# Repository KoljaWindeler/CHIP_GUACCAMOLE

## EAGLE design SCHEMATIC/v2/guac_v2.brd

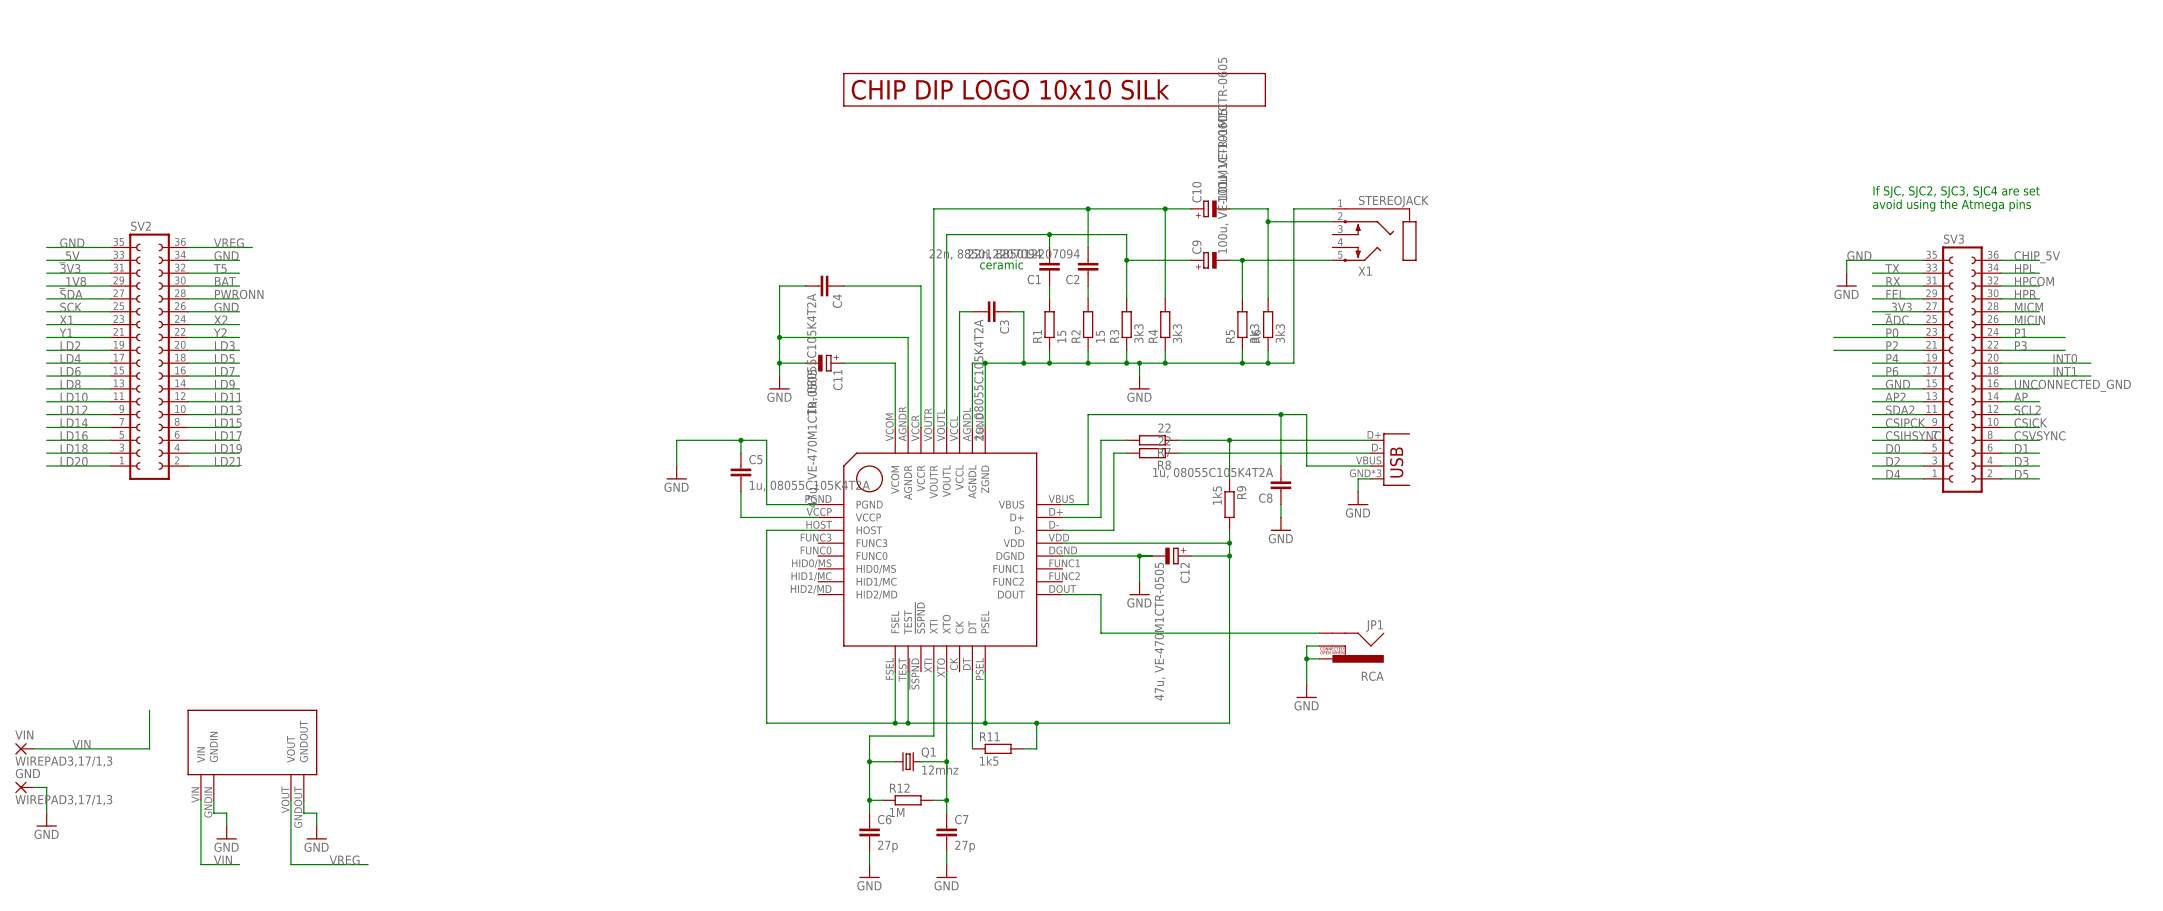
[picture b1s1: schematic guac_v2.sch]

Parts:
C1, C2: 22n, 885012207094; C0805
C3, C4, C5, C8: 1u, 08055C105K4T2A; C0805
C6, C7: 27p; C0805
C9, C10: 100u, VE-101M1CTR-0605; 140CLH-0810
C11, C12: 47u, VE-470M1CTR-0505; 140CLH-0810
GND: WIREPAD3,17/1,3; 3,17/1,3
JP1: RCA
Q1: 12mhz; HC49UP
R1, R2: 15; M0805
R3, R4, R5, R6: 3k3; M0805
R7, R8: 22; M0805
R9, R11: 1k5; M0805
R12: 1M; M0805
SV2, SV3: FE18-2
U$1: PCM2706; TQFP32-08
U$3: LOGO_10X10_SILK
U$9: MP1584EN_FRAMELESS
USB: USBUSB-MICROB-SMT-DIP; USB-MICROB-SMT-DIP
VIN: WIREPAD3,17/1,3; 3,17/1,3
X1: STEREOJACK; STX3100

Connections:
3V3: SV2.31
ADC: SV3.25
AP: SV3.14
AP2: SV3.13
BAT: SV2.30
CHIP_5V: SV3.36
CSICK: SV3.10
CSIHSYNC: SV3.7
CSIPCK: SV3.9
CSVSYNC: SV3.8
D0: SV3.5
D1: SV3.6
D2: SV3.3
D3: SV3.4
D4: SV3.1
D5: SV3.2
FEL: SV3.29
GND: C3.1, C4.2, C5.1, C6.2, C7.2, C8.1, C11.-, C12.-, GND.1, JP1.PIN, JP1.SWITCH, R1.1, R2.1, R3.1, R4.1, R5.1, R6.1, SV2.26, SV2.34, SV2.35, SV3.15, SV3.35, U$1.AGNDL, U$1.AGNDR, U$1.DGND, U$1.PGND, U$1.ZGND, U$9.GNDIN, U$9.GNDOUT, USB.GND, USB.MT1 (GND), USB.MT2 (GND), X1.1
HPCOM: SV3.32
HPL: SV3.34
HPR: SV3.30
INT0: SV3.20
INT1: SV3.18
LD2: SV2.19
LD3: SV2.20
LD4: SV2.17
LD5: SV2.18
LD6: SV2.15
LD7: SV2.16
LD8: SV2.13
LD9: SV2.14
LD10: SV2.11
LD11: SV2.12
LD12: SV2.9
LD13: SV2.10
LD14: SV2.7
LD15: SV2.8
LD16: SV2.5
LD17: SV2.6
LD18: SV2.3
LD19: SV2.4
LD20: SV2.1
LD21: SV2.2
MICIN: SV3.26
MICM: SV3.28
unnamed: C8.2, U$1.VBUS, USB.VBUS
unnamed: R7.2, U$1.D+
unnamed: R7.1, R9.1, USB.D+
unnamed: R8.2, U$1.D-
unnamed: R8.1, USB.D-
unnamed: JP1.SHELL, U$1.DOUT
unnamed: R11.1, U$1.DT
unnamed: C7.1, Q1.2, R12.2, U$1.XTO
unnamed: C6.1, Q1.1, R12.1, U$1.XTI
unnamed: C2.1, R2.2
unnamed: C5.2, U$1.VCCP
unnamed: C1.2, C9.+, R3.2, U$1.VOUTL
unnamed: C11.+, U$1.VCOM
unnamed: C2.2, C10.+, R4.2, U$1.VOUTR
unnamed: C4.1, U$1.VCCR
unnamed: C9.-, R5.2, X1.5
unnamed: C1.1, R1.2
unnamed: C10.-, R6.2, X1.2
unnamed: C3.2, U$1.VCCL
P0: SV3.23
P1: SV3.24
P2: SV3.21
P3: SV3.22
P4: SV3.19
P6: SV3.17
PWRONN: SV2.28
RX: SV3.31
SCK: SV2.25
SCL2: SV3.12
SDA: SV2.27
SDA2: SV3.11
T5: SV2.32
TX: SV3.33
UNCONNECTED_GND: SV3.16
VCC: C12.+, R9.2, R11.2, U$1.FSEL, U$1.HOST, U$1.PSEL, U$1.TEST, U$1.VDD
VIN: U$9.VIN, VIN.1
VREG: SV2.36, U$9.VOUT
X1: SV2.23
X2: SV2.24
Y1: SV2.21
Y2: SV2.22
_1V8: SV2.29
_3V3: SV3.27
_5V: SV2.33

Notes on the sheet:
If SJC, SJC2, SJC3, SJC4 are set avoid using the Atmega pins
ceramic

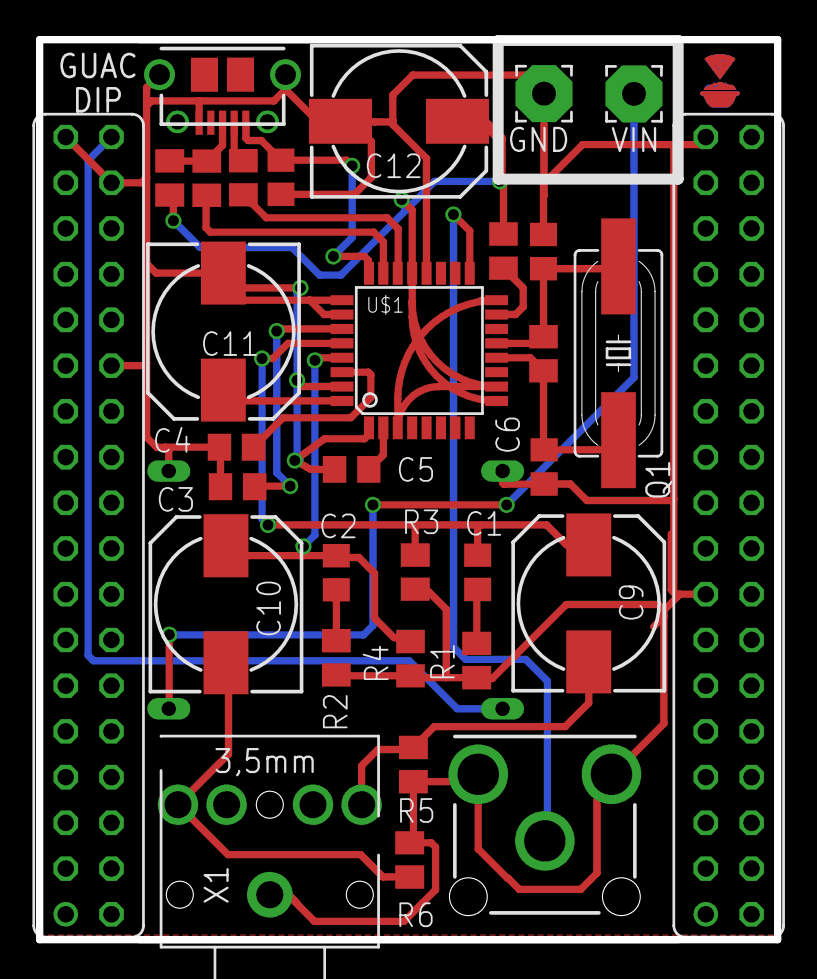
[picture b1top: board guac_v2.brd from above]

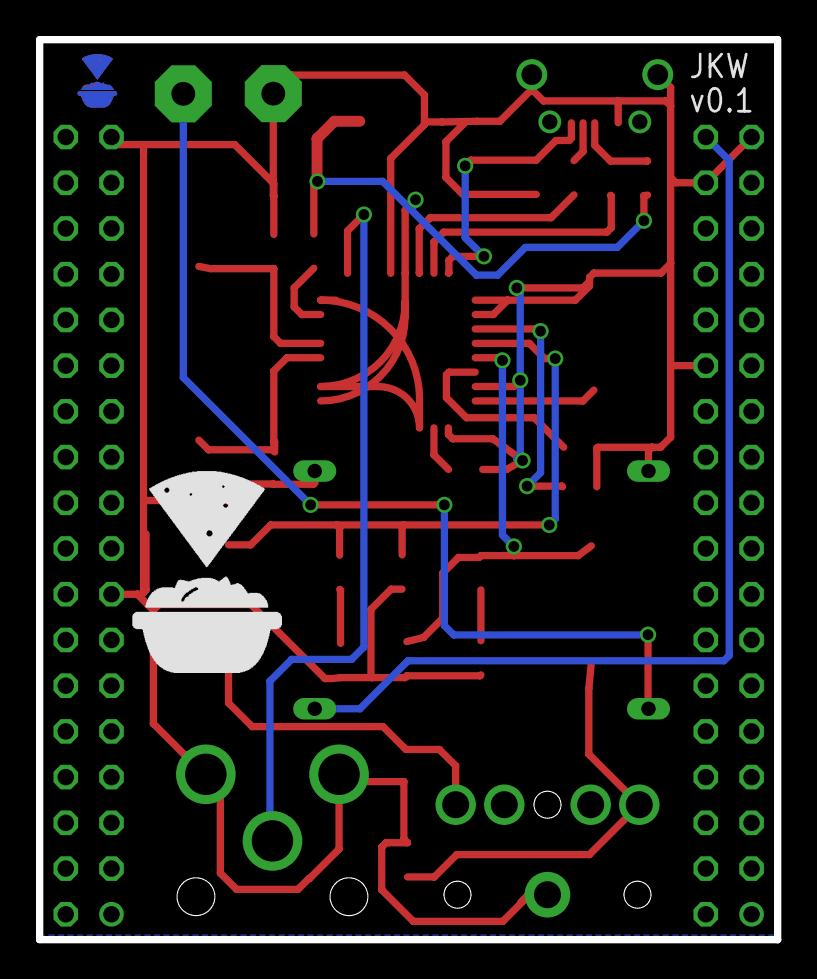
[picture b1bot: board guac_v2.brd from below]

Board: 2 copper layers, 41.0 x 50.0 mm, 36 parts (2 on the bottom side), 23 nets.

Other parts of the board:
U$2, U$5: LOGO

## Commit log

2016-03-25 :circus_tent: Added .gitattributes & .gitignore files
2016-03-25 init
2016-04-17 added radio commands
2016-04-17 guac with dcdc, smart idea?
2016-04-17 separated folder
2016-04-17 added stop script
2016-07-21 moved libs, dru, cam to common
2016-08-20 added cad files
2016-08-31 Added Descriptions

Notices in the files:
parts and their libraries:
SparkFun-Connectors: Licensing: Creative Commons ShareAlike 4.0 International - https://creativecommons.org/licenses/by-sa/4.0
